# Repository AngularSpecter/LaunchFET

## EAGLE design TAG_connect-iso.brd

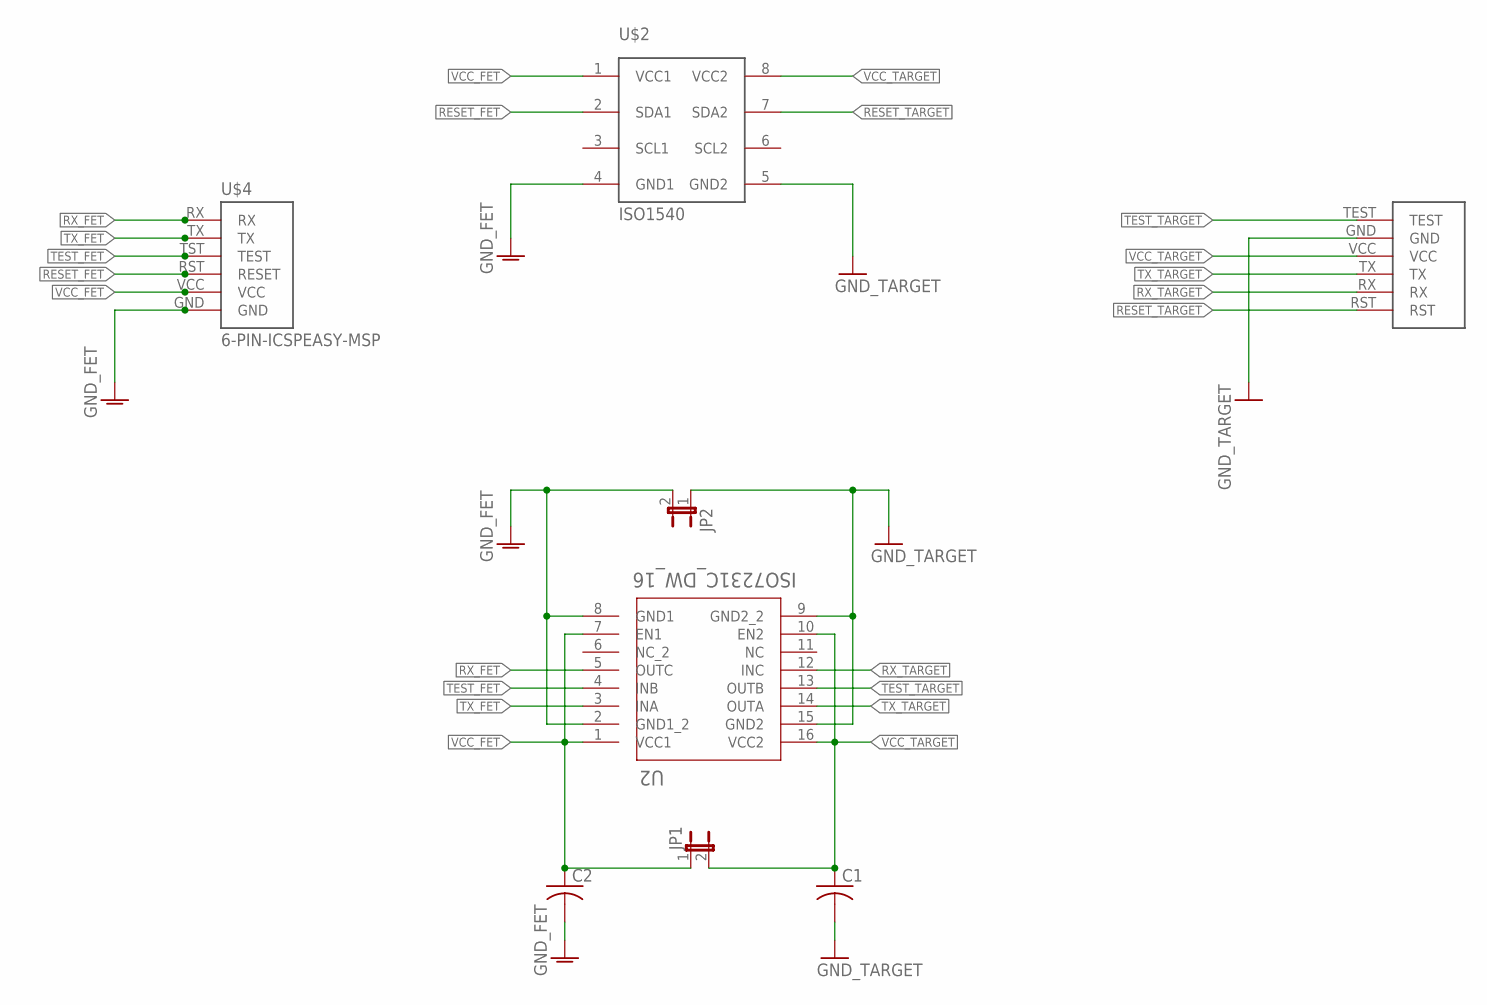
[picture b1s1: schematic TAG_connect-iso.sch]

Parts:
C1, C2: C-USC1206; C1206
JP1, JP2: JUMPER-2PTH_LOCK; 1X02_LOCK
U2: ISO7231C_DW_16; DW16
U$1: RJ-12SMD; MOLEX_RJ45_SMD
U$2: ISO1540; D8
U$4: 6-PIN-ICSPEASY-MSP; EASYMSP-6PIN

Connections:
GND_FET: C2.2, JP2.2, U2.2 (GND1_2), U2.8 (GND1), U$2.4 (GND1), U$4.GND
GND_TARGET: C1.2, JP2.1, U2.9 (GND2_2), U2.15 (GND2), U$1.GND, U$2.5 (GND2)
RESET_FET: U$2.2 (SDA1), U$4.RST (RESET)
RESET_TARGET: U$1.RST, U$2.7 (SDA2)
RX_FET: U2.5 (OUTC), U$4.RX
RX_TARGET: U2.12 (INC), U$1.RX
TEST_FET: U2.4 (INB), U$4.TST (TEST)
TEST_TARGET: U2.13 (OUTB), U$1.TEST
TX_FET: U2.3 (INA), U$4.TX
TX_TARGET: U2.14 (OUTA), U$1.TX
VCC_FET: C2.1, JP1.1, U2.1 (VCC1), U2.7 (EN1), U$2.1 (VCC1), U$4.VCC
VCC_TARGET: C1.1, JP1.2, U2.10 (EN2), U2.16 (VCC2), U$1.VCC, U$2.8 (VCC2)

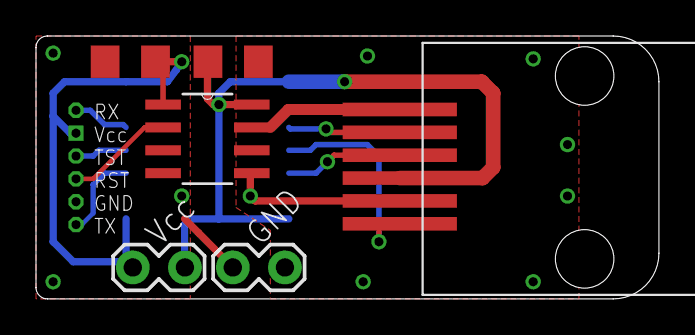
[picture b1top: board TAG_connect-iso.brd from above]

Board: 2 copper layers, 34.6 x 14.6 mm, 8 parts (1 on the bottom side), 12 nets.

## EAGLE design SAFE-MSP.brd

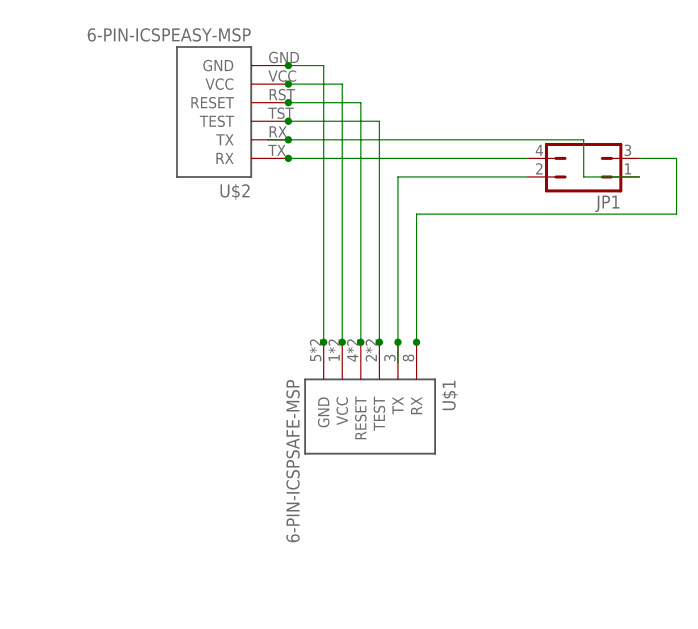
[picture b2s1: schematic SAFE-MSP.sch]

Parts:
JP1: JP2Q
U$1: 6-PIN-ICSPSAFE-MSP; SAFEMSP
U$2: 6-PIN-ICSPEASY-MSP; EASYMSP-6PIN

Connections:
GND: U$1.5 (GND), U$1.10 (GND), U$2.GND
RST: U$1.4 (RESET), U$1.9 (RESET), U$2.RST (RESET)
RX_FET: JP1.4, U$2.TX (RX)
RX_TARGET: JP1.3, U$1.8 (RX)
TST: U$1.2 (TEST), U$1.7 (TEST), U$2.TST (TEST)
TX_FET: JP1.1, U$2.RX (TX)
TX_TARGET: JP1.2, U$1.3 (TX)
VCC: U$1.1 (VCC), U$1.6 (VCC), U$2.VCC

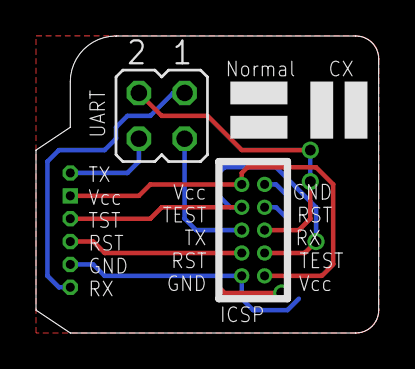
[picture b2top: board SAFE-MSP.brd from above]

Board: 2 copper layers, 19.0 x 16.5 mm, 3 parts (0 on the bottom side), 8 nets.

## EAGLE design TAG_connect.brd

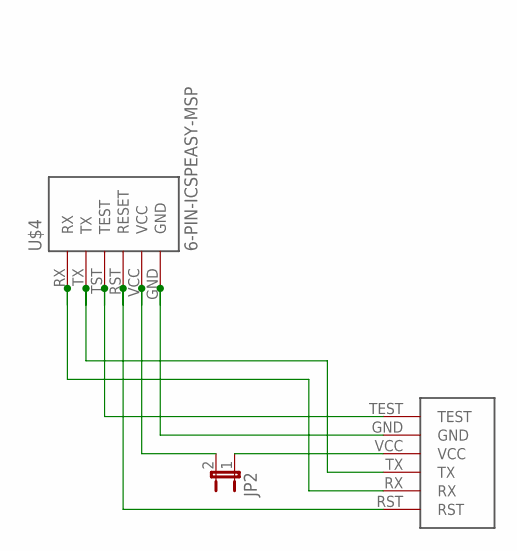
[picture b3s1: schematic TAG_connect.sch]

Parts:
JP2: JUMPER-2PTH_LOCK; 1X02_LOCK
U$1: RJ-45SMD; MOLEX_RJ45_SMD
U$4: 6-PIN-ICSPEASY-MSP; EASYMSP-6PIN

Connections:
GND: U$1.GND, U$4.GND
RST: U$1.RST, U$4.RST (RESET)
RX: U$1.RX, U$4.RX
TEST: U$1.TEST, U$4.TST (TEST)
TX: U$1.TX, U$4.TX
VCC_FET: JP2.2, U$4.VCC
VCC_TARGET: JP2.1, U$1.VCC

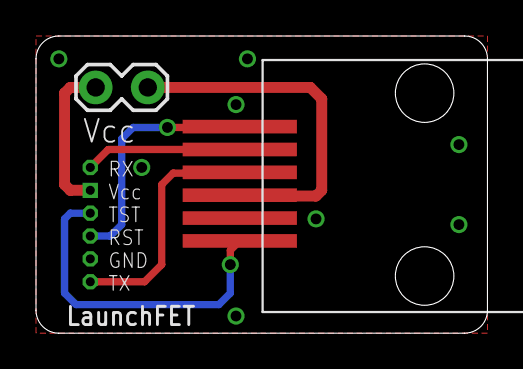
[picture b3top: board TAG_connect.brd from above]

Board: 2 copper layers, 25.1 x 16.5 mm, 3 parts (0 on the bottom side), 7 nets.

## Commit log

2014-05-04 new board, new pinout
    Changed the pinout on the tag-connect cable to match new work
    Added new SAFE-MSP adaptor board that uses a symmetric 2x10 .015" header
    for programming.
2014-05-04 bug fixes
    updated iso board to new pinout and rj-12 connector
    cleaned up safe-msp board

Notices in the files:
parts and their libraries:
SparkFun-Passives: Licensing: CC v3.0 Share-Alike You are welcome to use this library for commercial purposes.
